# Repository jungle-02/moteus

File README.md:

# moteus brushless servo #

This contains full designs for the moteus brushless servo actuator,
including firmware and PCBs.

**WARNING**: This is not just a software project.  It includes designs
for moderately high power electronics.  It has not yet burned down my
(or anyone's that I know of) house, but there are no guarantees.

# Specifications #

| Name                   | r4.11        | c1         | n1        | x1          |
|------------------------|--------------|------------|-----------|-------------|
| Voltage Input          | 10-44V       | 10-51V     | 10-54V    | 10-54V      |
| Peak Electrical Power  | 900W @ 30V   | 250W @ 28V | 2kW @ 36V | 1.3kW @ 36V |
| Mass                   | 14.2g        | 8.9g       | 14.6g     | 23.8g       |
| Control Rate           | 15-30kHz     | -          | -         | -           |
| PWM Switching Rate     | 15-60kHz     | -          | -         | -           |
| CPU                    | STM32G4      | -          | -         | -           |
| Uncooled phase current | 12A          | 5A         | 9A       | 25A         |
| Cooled phase current   | 32A          | 14A        | 26A       | 62A         |
| Peak phase current     | 100A         | 20A        | 100A      | 120A        |
| Communications         | 5Mbps CAN-FD | -          | -         | -           |
| Dimensions             | 46x53mm      | 38x38x9mm  | 46x46x8mm | 56x56x10mm  |

Assembled and tested boards can be purchased at: https://mjbots.com

# Directory structure #

* hw/ - hardware (mechanical and electrical designs)
  * controller/ - PCB design for moteus-r4.11
  * c1/ - PCB design for moteus-c1
  * n1/ - PCB design for moteus-n1
  * x1/ - PCB design for moteus-x1
* fw/ - firmware for brushless controller
* lib/ - client side software
* utils/ - diagnostic tools
* tools/ - bazel build configure
* docs/ - documentation

# Documentation #

* [Quick Start](https://mjbots.github.io/moteus/quick-start)
* [All Documentation](https://mjbots.github.io/moteus/)
* [Discord](https://discord.gg/W4hUpBb)

# Misc #

 * 

# How to support moteus development #

The easiest way to support development the moteus hardware and firmware is as follows:

1) Buy things from https://mjbots.com
2) Build awesome machines!

That's it!  If for some reason you want to go above and beyond, you can sponsor mjbots through github: https://github.com/sponsors/mjbots

# License #

All files contained in this repository, unless otherwise noted, are
available under an Apache 2.0 License:
https://www.apache.org/licenses/LICENSE-2.0

# Trademark #

mjbots Robotic Systems LLC owns and protects the "mjbots" and "moteus" trademarks in many jurisdictions.

If you want to use these names in your project or product, please read the [Trademark Policy](https://mjbots.com/trademark-policy)

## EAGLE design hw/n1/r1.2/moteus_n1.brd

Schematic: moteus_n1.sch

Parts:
A: PAD16AWG_TERM; 16AWG_TERM
AUX1: SM08B-GHS-TB(LF)(SN); JST_SM08B-GHS-TB(LF)(SN); MPN SM08B-GHS-TB(LF)(SN)
AUX2: SM07B-GHS-TB(LF)(SN); JST_SM07B-GHS-TB(LF)(SN); MPN SM07B-GHS-TB(LF)(SN)
B: PAD16AWG_TERM; 16AWG_TERM
C: PAD16AWG_TERM; 16AWG_TERM
C1, C19, C20, C21, C22, C25, C26, C27, C28, C29: DNP; C0402
C2: 1uF 100V; C0805; MPN GCM21BC72A105KE36L
C3, C17, C18, C23\, C24: 1uF; C0603; MPN MF-CAP-0603-1uF
C4, C13: 10uF; C1206; MPN MF-CAP-1206-10uF
C5, C10, C38, C40, C41: 1uF; C0402; MPN MF-CAP-0402-1uF
C6: 22uF; C1206; MPN CL31B226KPHNNNE
C7, C8, C9, C11, C12, C14, C15, C16, C30, C32, C33, C42: 0.1uF; C0402; MPN MF-CAP-0402-0.1uF
C31: 0.01uF; C0402; MPN MF-CAP-0402-0.01uF
C34, C35, C36: 1000pF; C0402; MPN MF-CAP-0402-1nF
C37, C39: 0.1uF 100V; C0603; MPN GCJ188R72A104KA01D
C43: 0.47uF 100V; C0805; MPN 08051C474KAT2A
C44, C45, C46: 0.1uF 100V; C1206; MPN 12061C104KAT2A
C47, C48: 4.7uF 100V; C1206; MPN GRJ31CC72A475KE01K
C49, C50, C51, C52, C53, C54, C55, C56, C57, C58, C59, C60, C61, C62, C63, C64, C65, C66, C67, C68, C69, C70, C71, C72, C73, C74, C75, C76, C77, C78, C79, C80, C81, C82, C83, C84, C85, C86: 4.7uF 100V; C1206_NOBORDER; MPN GRJ31CC72A475KE01K
CAN1, CAN2: JST-PH3; JST_S3B-PH-SM4-TB(LF)(SN); MPN S3B-PH-SM4-TB(LF)(SN)
CANG: PAD24AWG_PAD; 24AWG_PAD
CANH: PAD24AWG_PAD; 24AWG_PAD
CANL: PAD24AWG_PAD; 24AWG_PAD
D1: MF-LED-0603-RED; LED0603
D2: MF-LED-0603-RED; LED0603; MPN MF-LED-0603-GREEN
D3, D4, D5, D6, D7, D8, D9, D10, D11: BAT41KFILM; SODFL1608X70N; MPN BAT41KFILM
D12: DIODE-DO214AA; DO214AA; MPN SMBJ51D-M3/I
D33, D50: PAD24AWG_PAD; 24AWG_PAD
DAC: PAD24AWG_PAD; 24AWG_PAD
DG1: PAD24AWG_PAD; 24AWG_PAD
DTR: PAD24AWG_PAD; 24AWG_PAD
DTX: PAD24AWG_PAD; 24AWG_PAD
J1, J2: XT30XT30PW_MALE; XT30PW_MALE; MPN XT30PW-M
J3: SM06B-GHS-TB(LF)(SN); JST_SM06B-GHS-TB(LF)(SN); MPN SM06B-GHS-TB(LF)(SN)
L1: SRN4018-220M; IND_BOURNS_SRN4018; MANUFACTURER_PART_NUMBER 74404042470
L2: 74404024100; IND_4024100_WRE; MPN 74404024100
M1, M2, M3, M4: MOUNT; M2.5MOUNT
Q1, Q3, Q5: TPH1R204PL_VIAS; SOP_ADVANCE_8_VIAS; MPN TPH2R408QM,L1Q
Q2, Q4, Q6: TPH1R204PLSOP_ADVANCE_8; SOP_ADVANCE_8; MPN TPH2R408QM,L1Q
R1, R2: DNP; R0402
R3, R15: 100k 1%; R0402; MPN RC0402FR-07100KL
R4, R5, R8, R9, R10, R11, R12, R13, R14: 100; R0402; MPN MF-RES-0402-100
R6, R7, R25, R26, R33, R34: 2k; R0402; MPN MF-RES-0402-2K
R16: 4.7k 1%; R0402; MPN RC0402FR-074K7L
R17: 47k NTC; R0402; MPN NCP15WB473F03RC
R18, R19: 10k 1%; R0402; MPN RC0402FR-0710KL
R20, R21: 560; R0402; MPN MF-RES-0402-560
R22, R23, R24: 22; R0402; MPN MF-RES-0402-22
R27, R28, R30, R31, R32: 7.5; R0402; MPN RC0402FR-077R5L
R29: 7.5; R0805; MPN RC0805FR-077R5L
R35, R36: 120; R0402; MPN RC0402FR-07120RL
R37: DNP; R0805
RA: 0.5mOhm 1% 2W; M1206; MPN HCS1206FTL500
RB: 0.5mOhm 1% 2W; M1206; MPN HCS1206FTL500
RC: 0.5mOhm 1% 2W; M1206; MPN HCS1206FTL500
SH1, SH2, SH3: SHORTT5; SHORT_TOP-50
SH4: SHORTMEDIUM; SHORT_TOP-MEDIUM
SWD: JST-ZH6; JST_S6B-ZR-SM4A-TF(LF)(SN); MPN S6B-ZR-SM4A-TF(LF)(SN)
TEMP1, TEMP2: PAD24AWG_PAD; 24AWG_PAD
U1: MAX15062AATA+T; 21-0487A_MXM; MANUFACTURER_PART_NUMBER MAX15062BATA+T
U2: XC9265A331MR-G; SOT95P280X130-5N; MPN XC9265A331MR-G
U3: STM32G474CEU6; QFN50P700X700X60-49N; MPN STM32G474CEU6
U4: TCAN1042HGV; SOIC8; MPN TCAN1057AEVDRQ1
U5: AS5147; TSSOP14; MPN AS5047P-ATSM
U7: DRV8353S; WQFN-40; MPN DRV8353FSRTAR
U8: SN65HVD35DR; D14
VN: PAD16AWG_TERM; 16AWG_TERM
VP: PAD16AWG_TERM; 16AWG_TERM

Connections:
+3V3: AUX1.2, AUX2.2, C6.P$1, C7.P$1, C8.P$1, C10.P$1, C11.P$1, C12.P$1, C13.P$2, C15.P$1, C16.P$1, C18.P$1, C24.P$1, C30.P$1, C42.P$2, D33.P$1, L2.1, R2.P$2, R17.P$1, R20.P$1, R21.P$1, R25.P$1, R26.P$1, SWD.6, TEMP1.P$1, U2.4 (VOUT), U3.1 (VBAT), U3.20 (VREF+), U3.21 (VDDA), U3.23 (VDD_1), U3.35 (VDD_2), U3.48 (VDD_3), U4.5 (VIO), U5.12 (VDD3V), U7.24 (VREF), U8.13 (VCC_2), U8.14 (VCC)
+5V: AUX1.1, AUX2.1, C4.P$1, C5.P$1, C14.P$1, C17.P$1, C23\.P$1, D50.P$1, J3.1, L1.1, U1.4 (FB/VOUT), U2.1 (VIN), U2.3 (CE), U4.3 (VCC)
AS5047_CS: U3.19 (PB2), U5.1 (CS/)
AUX1_A: C29.P$1, R10.P$2, U3.13 (PA5), U3.27 (PB14), U5.2 (CLK)
AUX1_B: C28.P$1, R11.P$2, U3.42 (PB4), U5.3 (MISO)
AUX1_C: C27.P$1, R12.P$2, U3.15 (PA7), U5.4 (MOSI)
AUX1_D: C26.P$1, DTR.P$1, R13.P$2, R34.P$2, U3.38 (PA15), U8.2 (R)
AUX1_E: C25.P$1, DTX.P$1, R14.P$2, R33.P$2, U3.41 (PB3), U3.47 (PB9), U8.5 (D)
AUX1_I2C_PULLUP: R33.P$1, R34.P$1, U3.46 (PB8-BOOT0)
AUX2_A: C22.P$1, R4.P$2, U3.6 (PF1-OSC_OUT)
AUX2_B: C21.P$1, R5.P$2, R6.P$2, U3.5 (PF0-OSC_IN), U3.32 (PA10)
AUX2_C: C20.P$1, R7.P$2, R9.P$2, U3.16 (PC4), U3.33 (PA11)
AUX2_D: C19.P$1, R8.P$2, U3.45 (PB7)
AUX2_I2C_PULLUP: R6.P$1, R7.P$1, U3.34 (PA12)
CAN_N: CAN1.2, CAN2.2, CANL.P$1, R37.P$2, U4.6 (CANL)
CAN_P: CAN1.1, CAN2.1, CANH.P$1, R37.P$1, U4.7 (CANH)
CAN_RX: U3.43 (PB5), U4.4 (RXD)
CAN_TX: U3.44 (PB6), U4.1 (TXD)
CUR1: R22.P$1, U7.23 (SOA)
CUR2: R23.P$1, U7.22 (SOB)
CUR3: R24.P$1, U7.21 (SOC)
DAC: DAC.P$1, R2.P$1, R3.P$2, U3.12 (PA4)
DRV8323_CS: U3.17 (PB0), U7.30 (CS)
DRV8323_MISO: R25.P$2, U3.40 (PC11), U7.27 (MISO)
DRV8323_MOSI: U3.2 (PC13), U7.28 (MOSI)
DRV8323_SCLK: U3.39 (PC10), U7.29 (SCLK)
FCUR1: C34.P$1, R22.P$2, U3.11 (PA3)
FCUR2: C35.P$1, R23.P$2, U3.14 (PA6)
FCUR3: C36.P$1, R24.P$2, U3.18 (PB1)
GHA: D5.1 (K), R28.P$1, U7.6 (GHA)
GHA_D: D5.2 (A), Q1.4 (G), R28.P$2
GHB: D8.1 (K), R30.P$1, U7.15 (GHB)
GHB_D: D8.2 (A), Q3.4 (G), R30.P$2
GHC: D11.1 (K), R32.P$1, U7.16 (GHC)
GHC_D: D11.2 (A), Q5.4 (G), R32.P$2
GLA: D3.1 (K), R27.P$1, U7.8 (GLA)
GLA_D: D3.2 (A), D4.1 (K), Q2.4 (G), R27.P$2
GLB: D6.1 (K), R29.P$1, U7.13 (GLB)
GLB_D: D6.2 (A), D7.1 (K), Q4.4 (G), R29.P$2
GLC: D9.1 (K), R31.P$1, U7.18 (GLC)
GLC_D: D9.2 (A), D10.1 (K), Q6.4 (G), R31.P$2
GND: AUX1.8, AUX2.7, C3.P$2, C4.P$2, C5.P$2, C6.P$2, C7.P$2, C8.P$2, C9.P$2, C10.P$2, C11.P$2, C12.P$2, C13.P$1, C14.P$2, C15.P$2, C16.P$2, C17.P$2, C18.P$2, C19.P$2, C20.P$2, C21.P$2, C22.P$2, C23\.P$2, C24.P$2, C25.P$2, C26.P$2, C27.P$2, C28.P$2, C29.P$2, C30.P$2, C31.P$2, C32.P$2, C33.P$2, C34.P$2, C35.P$2, C36.P$2, C42.P$1, CAN1.3, CAN2.3, CANG.P$1, DG1.P$1, J3.6, R3.P$1, R16.P$1, R18.P$2, R19.P$2, SH4.2, SWD.4, U1.7 (GND), U2.2 (GND), U3.49 (THERMALPAD), U4.2 (GND), U4.8 (STB), U5.5 (TEST), U5.13 (GND), U7.25 (AGND), U8.6 (GND_2), U8.7 (GND)
LED1: D1.CATHODE, U3.28 (PB15)
LED2: D2.CATHODE, U3.29 (PC6)
MOTOR1: U3.8 (PA0), U7.32 (INHA)
MOTOR2: U3.9 (PA1), U7.34 (INHB)
MOTOR3: U3.10 (PA2), U7.36 (INHC)
MOTOR_ENABLE: U3.3 (PC14-OSC32_IN), U7.31 (ENABLE)
MOTOR_FAULT: R26.P$2, U3.26 (PB13), U7.26 (FAULT)
MOTOR_HIZ: U3.4 (PC15-OSC32_OUT), U7.33 (INLA), U7.35 (INLB), U7.37 (INLC)
unnamed: C1.P$1, M3.P$1, R1.P$1
unnamed: C40.P$2, U7.40 (VGLS)
unnamed: AUX2.3, R4.P$1
unnamed: C3.P$1, U1.3 (VCC)
unnamed: L2.2, U2.5 (LX)
unnamed: AUX2.4, R5.P$1
unnamed: AUX2.6, R8.P$1
unnamed: AUX2.5, R9.P$1
unnamed: AUX1.3, R10.P$1
unnamed: C39.P$2, U7.1 (CPL)
unnamed: AUX1.4, R11.P$1
unnamed: AUX1.5, R12.P$1
unnamed: C39.P$1, U7.2 (CPH)
unnamed: C38.P$2, U7.5 (VCP)
unnamed: AUX1.6, R13.P$1
unnamed: C41.P$2, U7.38 (DVDD)
unnamed: D1.ANODE, R20.P$2
unnamed: D2.ANODE, R21.P$2
unnamed: AUX1.7, R14.P$1
NRST: C9.P$1, SWD.2, U3.7 (PG10-NRST)
RS422_A: J3.2, R35.P$2, U8.12 (A)
RS422_B: J3.3, R35.P$1, U8.11 (B)
RS422_DE: U3.24 (PB11), U8.4 (DE)
RS422_RE: U3.22 (PB10), U8.3 (!RE)
RS422_Y: J3.4, R36.P$2, U8.9 (Y)
RS422_Z: J3.5, R36.P$1, U8.10 (Z)
SHA: A.1, A.2, A.3, A.4, A.5, A.6, A.7, A.8, A.9, A.10, A.11, A.12, Q1.1 (S), Q1.2 (S), Q1.3 (S), Q2.5 (D), Q2.6 (D), Q2.7 (D), Q2.8 (D), Q2.PAD (D), U7.7 (SHA)
SHB: B.1, B.2, B.3, B.4, B.5, B.6, B.7, B.8, B.9, B.10, B.11, B.12, Q3.1 (S), Q3.2 (S), Q3.3 (S), Q4.5 (D), Q4.6 (D), Q4.7 (D), Q4.8 (D), Q4.PAD (D), U7.14 (SHB)
SHC: C.1, C.2, C.3, C.4, C.5, C.6, C.7, C.8, C.9, C.10, C.11, C.12, Q5.1 (S), Q5.2 (S), Q5.3 (S), Q6.5 (D), Q6.6 (D), Q6.7 (D), Q6.8 (D), Q6.PAD (D), U7.17 (SHC)
SWCLK: SWD.5, U3.37 (PA14)
SWDIO: SWD.3, U3.36 (PA13)
SXA_N: SH1.1, U7.10 (SNA)
SXA_P: C44.P$2, Q2.1 (S), Q2.2 (S), Q2.3 (S), RA.2, U7.9 (SPA)
SXB_N: SH2.1, U7.11 (SNB)
SXB_P: C45.P$2, Q4.1 (S), Q4.2 (S), Q4.3 (S), RB.2, U7.12 (SPB)
SXC_N: SH3.1, U7.20 (SNC)
SXC_P: C46.P$2, Q6.1 (S), Q6.2 (S), Q6.3 (S), RC.2, U7.19 (SPC)
V+: C2.P$1, C37.P$1, C38.P$1, C43.P$1, C44.P$1, C45.P$1, C46.P$1, C47.P$1, C48.P$1, C49.P$1, C50.P$1, C51.P$1, C52.P$1, C53.P$1, C54.P$1, C55.P$1, C56.P$1, C57.P$1, C58.P$1, C59.P$1, C60.P$1, C61.P$1, C62.P$1, C63.P$1, C64.P$1, C65.P$1, C66.P$1, C67.P$1, C68.P$1, C69.P$1, C70.P$1, C71.P$1, C72.P$1, C73.P$1, C74.P$1, C75.P$1, C76.P$1, C77.P$1, C78.P$1, C79.P$1, C80.P$1, C81.P$1, C82.P$1, C83.P$1, C84.P$1, C85.P$1, C86.P$1, D12.C, J1.1, J2.1, Q1.5 (D), Q1.6 (D), Q1.7 (D), Q1.8 (D), Q1.PAD (D), Q3.5 (D), Q3.6 (D), Q3.7 (D), Q3.8 (D), Q3.PAD (D), Q5.5 (D), Q5.6 (D), Q5.7 (D), Q5.8 (D), Q5.PAD (D), R15.P$2, U1.1 (VIN), U1.2 (EN/UVLO), U7.3 (VM), U7.4 (VDRAIN), VP.1, VP.2, VP.3, VP.4, VP.5, VP.6, VP.7, VP.8, VP.9, VP.10, VP.11, VP.12
V-: C1.P$2, C2.P$2, C37.P$2, C40.P$1, C41.P$1, C43.P$2, C47.P$2, C48.P$2, C49.P$2, C50.P$2, C51.P$2, C52.P$2, C53.P$2, C54.P$2, C55.P$2, C56.P$2, C57.P$2, C58.P$2, C59.P$2, C60.P$2, C61.P$2, C62.P$2, C63.P$2, C64.P$2, C65.P$2, C66.P$2, C67.P$2, C68.P$2, C69.P$2, C70.P$2, C71.P$2, C72.P$2, C73.P$2, C74.P$2, C75.P$2, C76.P$2, C77.P$2, C78.P$2, C79.P$2, C80.P$2, C81.P$2, C82.P$2, C83.P$2, C84.P$2, C85.P$2, C86.P$2, D4.2 (A), D7.2 (A), D10.2 (A), D12.A, J1.2, J2.2, R1.P$2, RA.1, RB.1, RC.1, SH1.2, SH2.2, SH3.2, SH4.1, U7.39 (GND), U7.PAD, VN.1, VN.2, VN.3, VN.4, VN.5, VN.6, VN.7, VN.8, VN.9, VN.10, VN.11, VN.12
VBAT_SENSE: C31.P$1, R15.P$1, R16.P$2, U3.31 (PA9)
VSW: L1.2, U1.8 (LX)
VTEMP_FET: C32.P$1, R17.P$2, R18.P$1, U3.25 (PB12)
VTEMP_MOT: C33.P$1, R19.P$1, TEMP2.P$1, U3.30 (PA8)

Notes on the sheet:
PCB rev divider HI / LO r1.1 - open / 100k

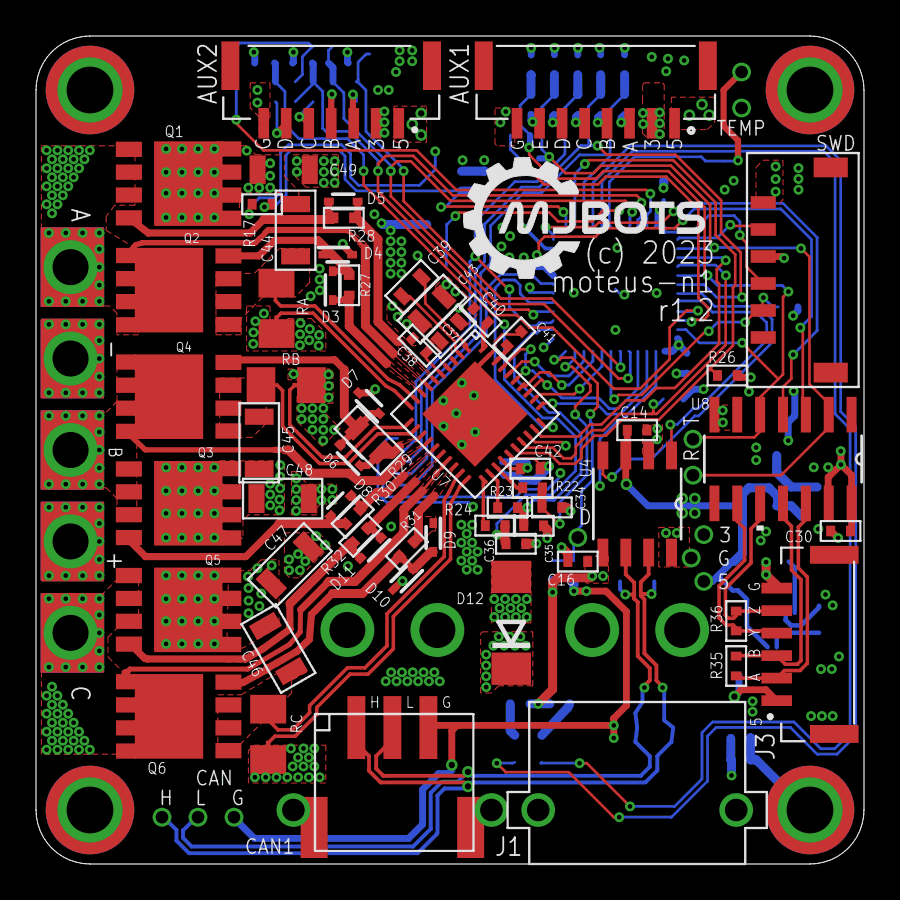
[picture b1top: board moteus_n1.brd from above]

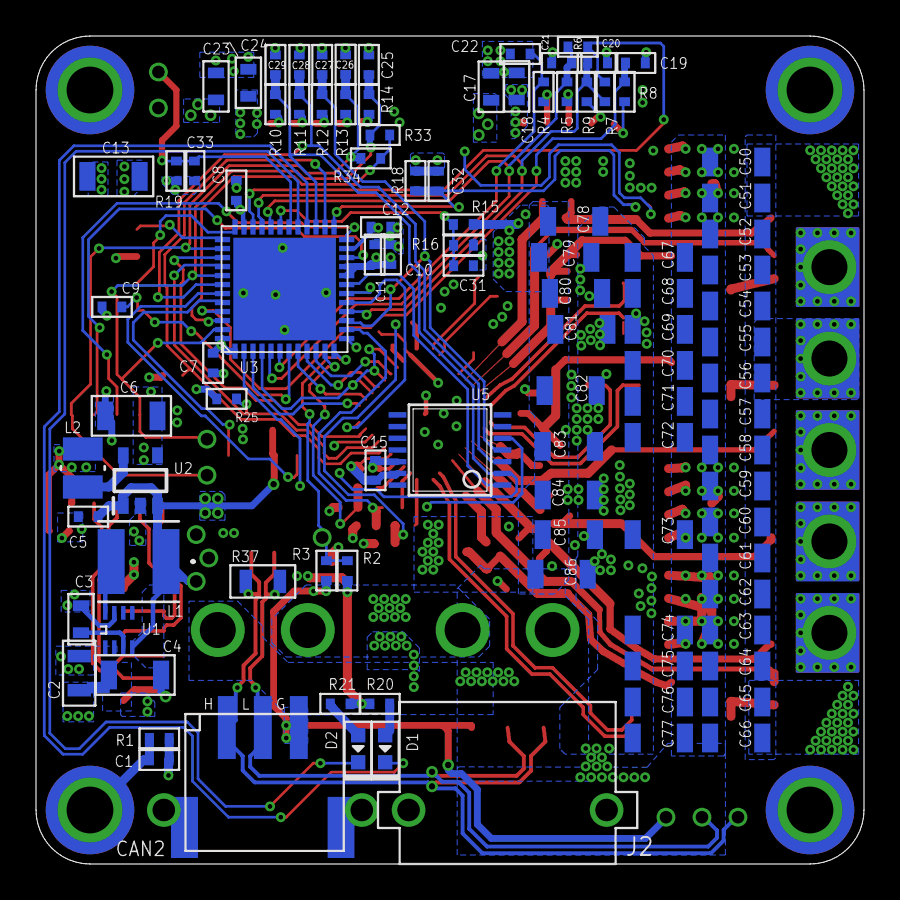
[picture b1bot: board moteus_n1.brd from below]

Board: 4 copper layers, 46.0 x 46.0 mm, 185 parts (107 on the bottom side), 93 nets.

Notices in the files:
hw/controller/r4.11/controller.sch:
Licensed under the Apache 2.0 License
hw/controller/r4.3/controller.brd:
(c) 2020
hw/controller/r4.8/controller.brd:
(c) 2021
hw/n1/r1.2/moteus_n1.brd:
(c) 2023
parts and their libraries:
power_dist: COPYRIGHT: Copyright (C) 2018 Accelerated Designs. All rights reserved
moteus_hp: COPYRIGHT: Copyright (C) 2022 Ultra Librarian. All rights reserved.
moteus_n1: COPYRIGHT: Copyright (C) 2023 Ultra Librarian. All rights reserved.
